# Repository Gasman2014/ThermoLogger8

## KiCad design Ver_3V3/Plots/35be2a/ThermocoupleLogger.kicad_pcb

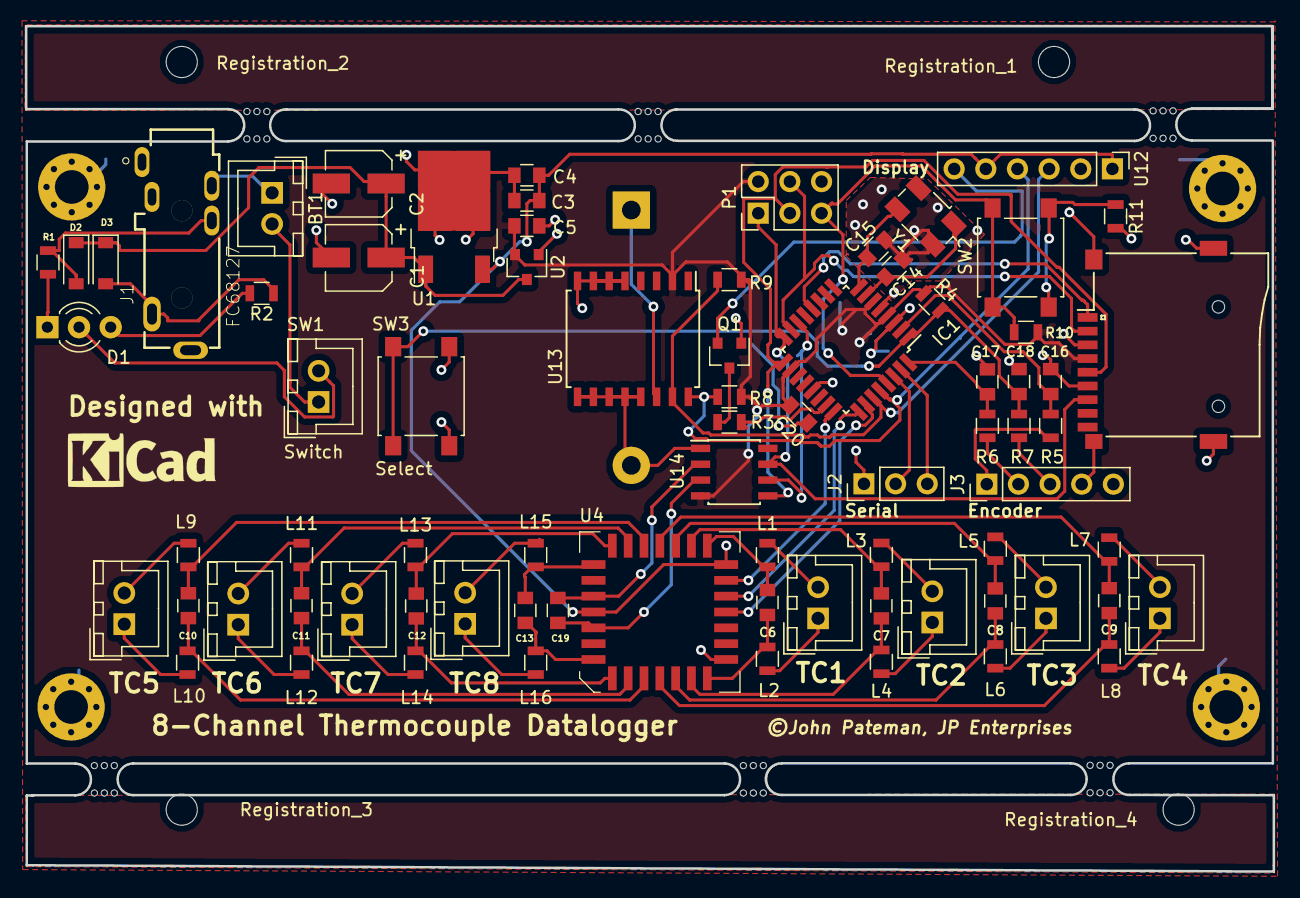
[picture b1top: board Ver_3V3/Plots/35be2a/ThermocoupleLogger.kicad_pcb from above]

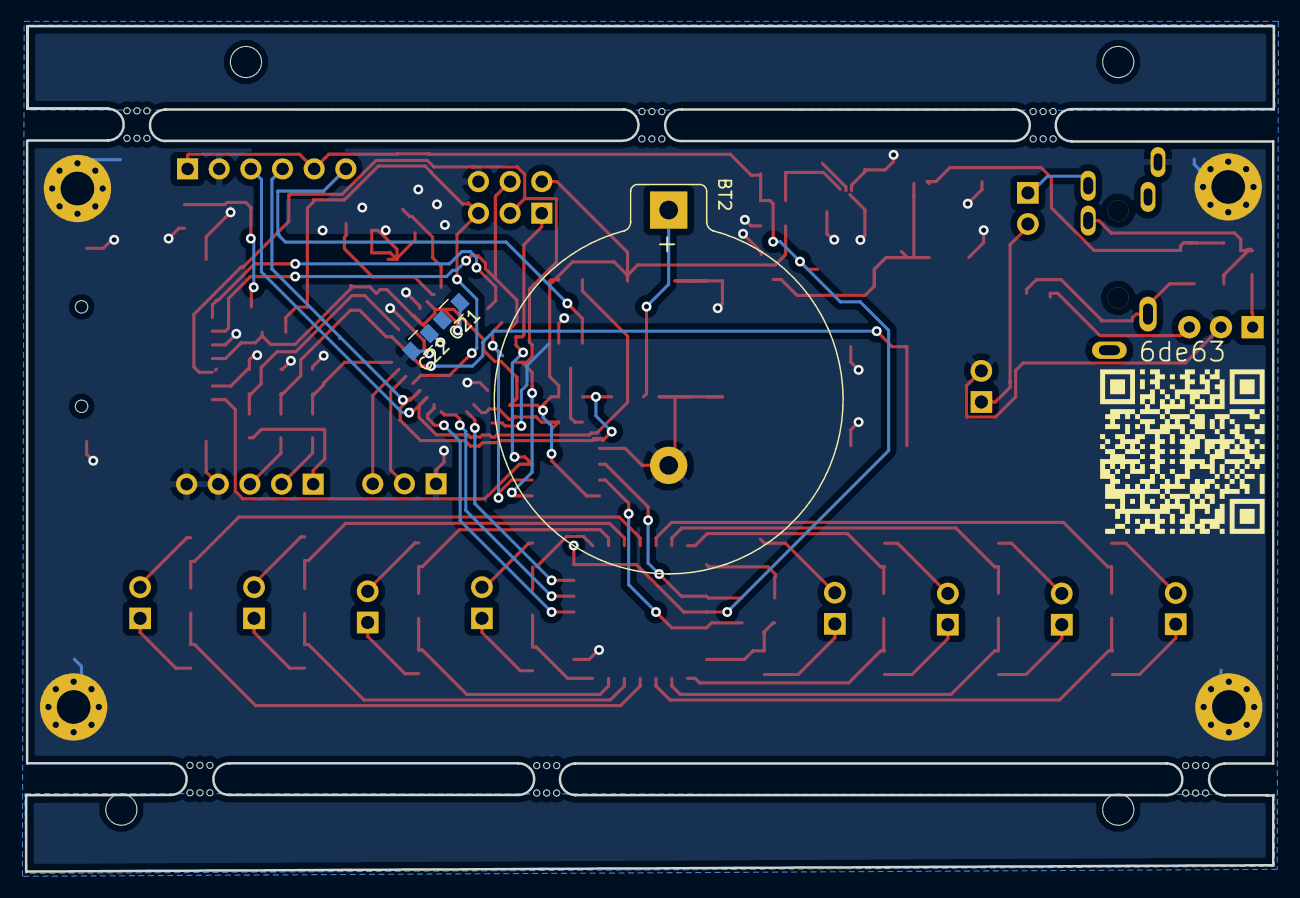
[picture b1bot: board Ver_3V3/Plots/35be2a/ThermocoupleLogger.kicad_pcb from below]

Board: 2 copper layers, 100.1 x 67.8 mm, 94 parts (5 on the bottom side), 70 nets.

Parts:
BT1: Battery; JST_XH_B02B-XH-A_02x2.50mm_Straight
BT2: 3V [CR2032]; Keystone_106_1x20mm-CoinCell
C1, C2: 100uF; CP_Elec_5x5.3
C3, C5, C16, C17, C18, C20, C21, C22: 100nF; C_0805
C4: 10uF; C_0805
C6, C7, C8, C9, C10, C11, C12, C13, C14, C15, C19: 10nF; C_0805
CON1: SD_Card; Conn_uSDcard
D1: LED_Dual_ACA; LED_D3.0mm-3
D2, D3: 1N4448W-7-F; D_SOD-123
IC1: ATMEGA328-P; TQFP-32_7x7mm_Pitch0.8mm
J1: FC68127; CLIFF_FC68127
J2: CONN_01X03; Pin_Header_Straight_1x03_Pitch2.54mm
J3: CONN_01X05; Pin_Header_Straight_1x05_Pitch2.54mm
L1, L2, L3, L4, L5, L6, L7, L8, L9, L10, L11, L12, L13, L14, L15, L16: Ferrite_Bead_Small; L_0805
MK1, MK2, MK3, MK4: Mounting_Hole; MountingHole_2.7mm_M2.5_Pad_Via
P1: CONN_02X03; Pin_Header_Straight_2x03_Pitch2.54mm
Q1: BD139; SOT-23
QR*****: 6de63
R1, R2: 750R; R_0805
R3, R4, R10: 10k; R_0805
R5, R6, R7: 22k; R_0805
R8, R9: 4.7k; R_0805
R11: 330R; R_0805
Registration_1, Registration_2, Registration_3, Registration_4: Alignment_Hole_2.5mm
SW1: SW_SPST; JST_XH_B02B-XH-A_02x2.50mm_Straight
SW2, SW3: SW_PUSH; SW_SPST_B3S-1000
U1: LF50_TO252; TO-252-2
U2: MCP1703A-3302_SOT23; SOT-23
U3, U5, U6, U7, U8, U9, U10, U11: TC_Connector; JST_XH_B02B-XH-A_02x2.50mm_Straight
U4: ADG407BPZ; PLCC-28
U12: I2C_20x4_DISPLAY; Pin_Header_Straight_1x06_Pitch2.54mm
U13: DS3231; SOIC-16W_7.5x10.3mm_Pitch1.27mm
U14: MAX31855KASA; SOIC-8_3.9x4.9mm_Pitch1.27mm
Y1: Crystal_8MHz; Crystal_SMD_Abracon_ABM3B-4pin_5.0x3.2mm
mouse-bite-2.54mm-slot, mouse-bite-2.54mm-slot#2, mouse-bite-2.54mm-slot#3, mouse-bite-2.54mm-slot#4, mouse-bite-2.54mm-slot#5, mouse-bite-2.54mm-slot#6: VAL**; mouse-bite-2.54mm-slot

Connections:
3V3: C5.1, C20.1, C21.1, C22.1, CON1.4, IC1.4, IC1.6, IC1.18, P1.2, R4.1, R8.1, R9.1, R10.1, U2.2, U13.2, U14.4
5V0: C3.1, C4.1, U1.3, U4.1, U4.18, U12.1, U12.5
9V0: C1.1, C2.1, D2.1, D3.1, U1.1, U2.3
/Thermocouple connectors/SA1: C6.1, L1.1, U4.19
/Thermocouple connectors/SA2: C7.1, L3.1, U4.20
/Thermocouple connectors/SA3: C8.1, L5.1, U4.21
/Thermocouple connectors/SA4: C9.1, L7.1, U4.22
/Thermocouple connectors/SA5: C10.1, L9.1, U4.23
/Thermocouple connectors/SA6: C11.1, L11.1, U4.24
/Thermocouple connectors/SA7: C12.1, L13.1, U4.25
/Thermocouple connectors/SA8: C13.1, L15.1, U4.26
/Thermocouple connectors/SB1: C6.2, L2.2, U4.11
/Thermocouple connectors/SB2: C7.2, L4.2, U4.10
/Thermocouple connectors/SB3: C8.2, L6.2, U4.9
/Thermocouple connectors/SB4: C9.2, L8.2, U4.8
/Thermocouple connectors/SB5: C10.2, L10.2, U4.7
/Thermocouple connectors/SB6: C11.2, L12.2, U4.6
/Thermocouple connectors/SB7: C12.2, L14.2, U4.5
/Thermocouple connectors/SB8: C13.2, L16.2, U4.4
B_LIGHT: IC1.23, R3.1
DA_MUX: C19.2, U4.28, U14.2
DB_MUX: C19.1, U4.2, U14.3
ENC_A: C17.1, IC1.32, R6.2
ENC_B/SW1: C18.1, IC1.1, R4.2, R7.2, SW3.1
ENC_SW: C16.1, IC1.2, R5.2
GND: BT2.2, C1.2, C2.2, C3.2, C4.2, C5.2, C14.1, C15.1, C16.2, C17.2, C18.2, C20.2, C22.2, CON1.3, CON1.6, D1.2, IC1.3, IC1.5, IC1.21, J1.1, J2.1, J3.4, J3.5, MK1.1, MK2.1, MK3.1, MK4.1, P1.6, Q1.1, R11.2, SW1.2, SW3.2, U1.2, U2.1, U4.12, U12.2, U13.5, U13.6, U13.7, U13.8, U13.9, U13.10, U13.11, U13.12, U13.13, U14.1, Y1.2, Y1.4
MISO: CON1.7, IC1.16, P1.1, U14.7
MOSI: CON1.2, IC1.15, P1.4
unnamed: BT1.1, J1.4
unnamed: BT1.2, SW1.1
unnamed: BT2.1, U13.14
unnamed: C14.2, IC1.7, Y1.1
unnamed: C15.2, IC1.8, Y1.3
unnamed: D1.1, R1.2
unnamed: D1.3, R2.2
unnamed: D2.2, J1.2, R1.1
unnamed: D3.2, J1.3, R2.1
unnamed: J3.1, R5.1
unnamed: J3.2, R6.1
unnamed: J3.3, R7.1
unnamed: L1.2, U3.2
unnamed: L2.1, U3.1
unnamed: L3.2, U5.2
unnamed: L4.1, U5.1
unnamed: L5.2, U6.2
unnamed: L6.1, U6.1
unnamed: L7.2, U7.2
unnamed: L8.1, U7.1
unnamed: L9.2, U8.2
unnamed: L10.1, U8.1
unnamed: L11.2, U9.2
unnamed: L12.1, U9.1
unnamed: L13.2, U10.2
unnamed: L14.1, U10.1
unnamed: L15.2, U11.2
unnamed: L16.1, U11.1
unnamed: Q1.2, U12.6
unnamed: Q1.3, R3.2
unnamed: R11.1, SW2.2
RESET: IC1.29, P1.5, R10.2, SW2.1
Rx: IC1.30, J2.2
SCK: CON1.5, IC1.17, P1.3, U14.5
SCL: IC1.28, R8.2, U12.4, U13.16
SDA: IC1.27, R9.2, U12.3, U13.15
SLCT0: IC1.24, U4.17
SLCT1: IC1.25, U4.16
SLCT2: IC1.26, U4.15
SS0: CON1.1, IC1.12
SS1: IC1.14, U14.6
Tx: IC1.31, J2.3

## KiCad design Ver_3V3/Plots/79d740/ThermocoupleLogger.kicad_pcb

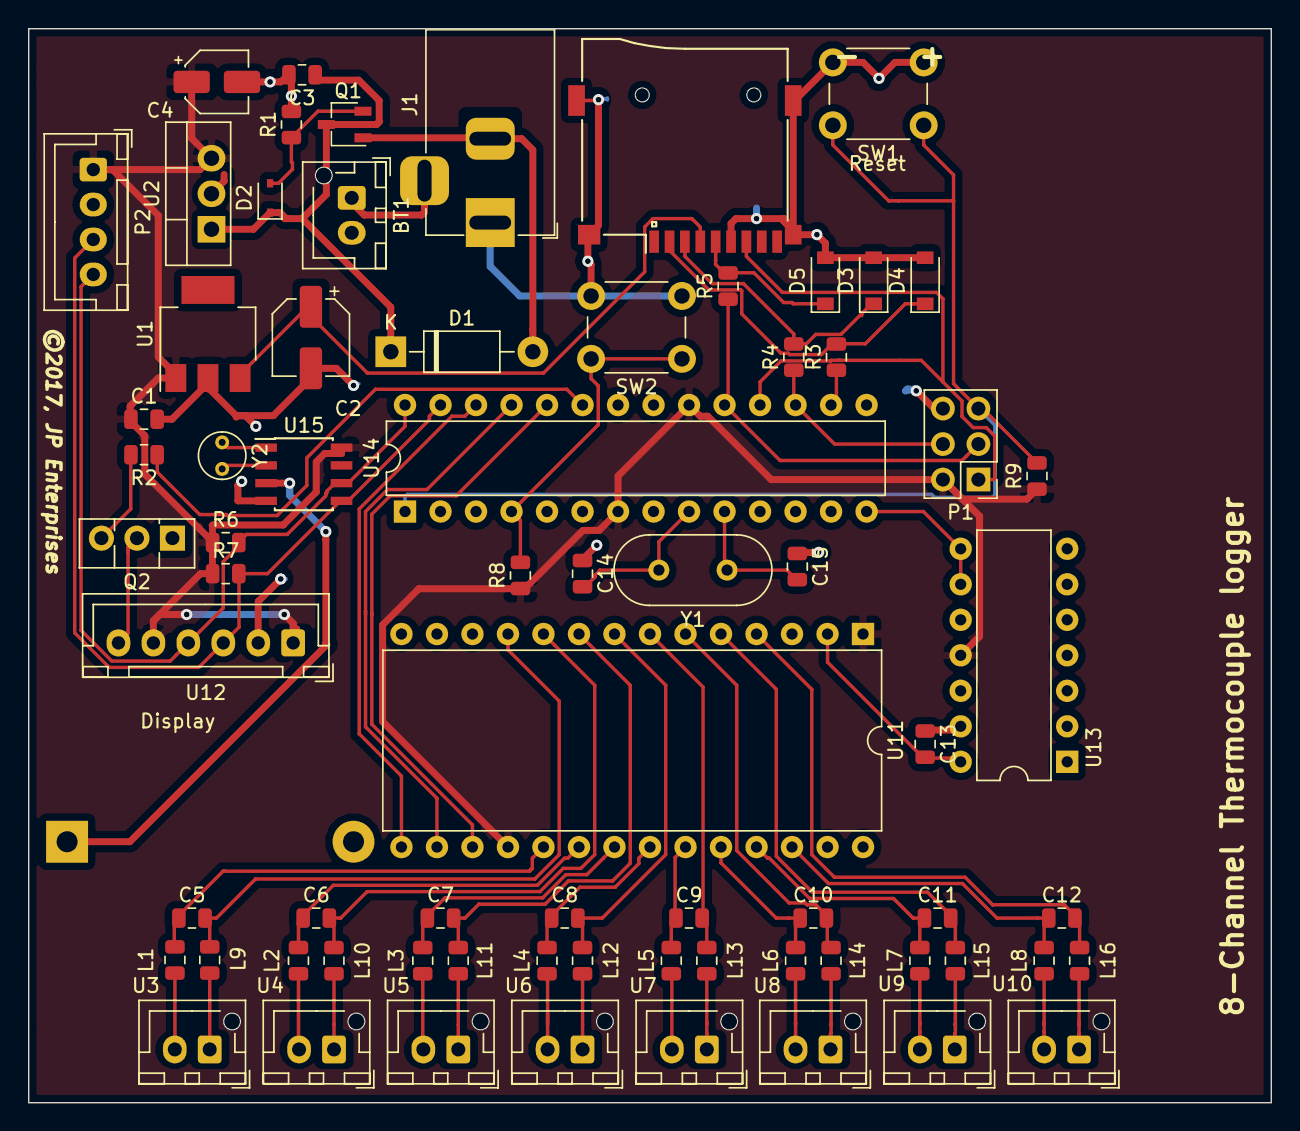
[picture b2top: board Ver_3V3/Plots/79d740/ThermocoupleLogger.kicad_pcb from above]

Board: 2 copper layers, 88.9 x 76.8 mm, 72 parts (1 on the bottom side), 63 nets.

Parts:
BT1: 9V; JST_XH_B02B-XH-AM_1x02_P2.50mm_Vertical
BT2: Battery; BatteryHolder_Keystone_103_1x20mm
C1: 470nF; C_0805_2012Metric
C2: 47uF; CP_Elec_5x5.3
C3: 1uF; C_0805_2012Metric
C4: 10uF; CP_Elec_4x5.4
C5, C6, C7, C8, C9, C10, C11, C12, C13: 10nF; C_0805_2012Metric
C14, C15: 18pF; C_0805_2012Metric
D1: 1N4007; D_DO-41_SOD81_P10.16mm_Horizontal
D2: 9V; D_SOD-323
D3, D4, D5: 3.3V; D_SOD-123
J1: Barrel_Jack; BarrelJack_Horizontal
L1, L2, L3, L4, L5, L6, L7, L8, L9, L10, L11, L12, L13, L14, L15, L16: 150; L_0805_2012Metric
P1: CONN_02X03; PinHeader_2x03_P2.54mm_Vertical
P2: Conn_01x04; JST_XH_B04B-XH-A_1x04_P2.50mm_Vertical
Q1: BS250; TSOT-23
Q2: BD139; TO-126-3_Vertical
R1, R2, R8, R9: 10K; R_0805_2012Metric
R3, R4, R5: 220R; R_0805_2012Metric
R6, R7: 5.1K; R_0805_2012Metric
SW1, SW2: SW_Push; SW_PUSH_6mm_H5mm
U1: LM3940; SOT-223
U2: 7805; TO-220-3_Vertical
U3, U4, U5, U6, U7, U8, U9, U10: TC_Connector; JST_XH_B02B-XH-AM_1x02_P2.50mm_Vertical
U11: ADG407; DIP-28_W15.24mm
U12: I2C_20x4_DISPLAY; JST_XH_B06B-XH-A_1x06_P2.50mm_Vertical
U13: AD595; DIP-14_W7.62mm
U14: ATMEGA328P-PU; DIP-28_W7.62mm
U15: DS1307+; SOIC-8_3.9x4.9mm_P1.27mm
XS1: SD_ebay-uSD-push/push_SMD; Conn_uSDcard
Y1: 16MHz; Crystal_HC49-U_Vertical
Y2: 32.768kHz; Crystal_Round_D3.0mm_Vertical

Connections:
3V3: C2.1, U1.3, XS1.4
5V0: C1.1, C4.1, P1.2, P2.1, R6.1, R7.1, R8.1, R9.1, U1.1, U2.3, U11.1, U11.18, U12.1, U12.5, U13.11, U14.7, U14.20, U15.8
9V0: C3.1, D1.1, D2.1, Q1.3, U2.1
/Thermocouple connectors/SA1: C5.1, L1.1, U11.19
/Thermocouple connectors/SA2: C6.1, L2.1, U11.20
/Thermocouple connectors/SA3: C7.1, L3.1, U11.21
/Thermocouple connectors/SA4: C8.1, L4.1, U11.22
/Thermocouple connectors/SA5: C9.1, L5.1, U11.23
/Thermocouple connectors/SA6: C10.1, L6.1, U11.24
/Thermocouple connectors/SA7: C11.1, L7.1, U11.25
/Thermocouple connectors/SA8: C12.1, L8.1, U11.26
/Thermocouple connectors/SB1: C5.2, L9.2, U11.11
/Thermocouple connectors/SB2: C6.2, L10.2, U11.10
/Thermocouple connectors/SB3: C7.2, L11.2, U11.9
/Thermocouple connectors/SB4: C8.2, L12.2, U11.8
/Thermocouple connectors/SB5: C9.2, L13.2, U11.7
/Thermocouple connectors/SB6: C10.2, L14.2, U11.6
/Thermocouple connectors/SB7: C11.2, L15.2, U11.5
/Thermocouple connectors/SB8: C12.2, L16.2, U11.4
/Thermocouple_PSU/Supply: D1.2, J1.2, Q1.1
B_LIGHT: R2.1, U14.23
DB_MUX: C13.2, U11.2, U13.14
GND: BT1.2, BT2.2, C1.2, C2.2, C3.2, C4.2, C13.1, C14.1, C15.1, D3.2, D4.2, D5.2, J1.1, P1.6, P2.2, Q2.1, R1.2, SW1.2, SW2.2, U1.2, U2.2, U11.12, U11.28, U12.2, U13.1, U13.4, U13.7, U13.13, U14.8, U14.22, U15.4, XS1.6
MISO: P1.1, U14.18, XS1.7
MOSI: P1.4, R4.1, U14.17
unnamed: BT1.1, J1.3
unnamed: BT2.1, U15.3
unnamed: C14.2, U14.9, Y1.2
unnamed: C15.2, U14.10, Y1.1
unnamed: U15.1, Y2.1
unnamed: U15.2, Y2.2
unnamed: D2.2, Q1.2, R1.1
unnamed: D3.1, R4.2, XS1.3
unnamed: D4.1, R3.2, XS1.2
unnamed: D5.1, R5.2, XS1.5
unnamed: L1.2, U3.2
unnamed: L2.2, U4.2
unnamed: L3.2, U5.2
unnamed: L4.2, U6.2
unnamed: L5.2, U7.2
unnamed: L6.2, U8.2
unnamed: L7.2, U9.2
unnamed: L8.2, U10.2
unnamed: L9.1, U3.1
unnamed: L10.1, U4.1
unnamed: L11.1, U5.1
unnamed: L12.1, U6.1
unnamed: L13.1, U7.1
unnamed: L14.1, U8.1
unnamed: L15.1, U9.1
unnamed: L16.1, U10.1
unnamed: Q2.2, U12.6
unnamed: Q2.3, R2.2
unnamed: R8.2, SW2.1, U14.4
RESET: P1.5, R9.2, SW1.1, U14.1
SCK: P1.3, R5.1, U14.19
SCL: P2.4, R6.2, U12.4, U14.28, U15.6
SDA: P2.3, R7.2, U12.3, U14.27, U15.5
SLCT0: U11.17, U14.24
SLCT1: U11.16, U14.25
SLCT2: U11.15, U14.26
SS: R3.1, U14.16
TEMP: U13.8, U13.9, U14.14

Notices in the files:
Ver_3V3/Plots/35be2a/ThermocoupleLogger.kicad_pcb:
©John Pateman, JP Enterprises
Ver_3V3/Plots/79d740/ThermocoupleLogger.kicad_pcb:
©2017, JP Enterprises
